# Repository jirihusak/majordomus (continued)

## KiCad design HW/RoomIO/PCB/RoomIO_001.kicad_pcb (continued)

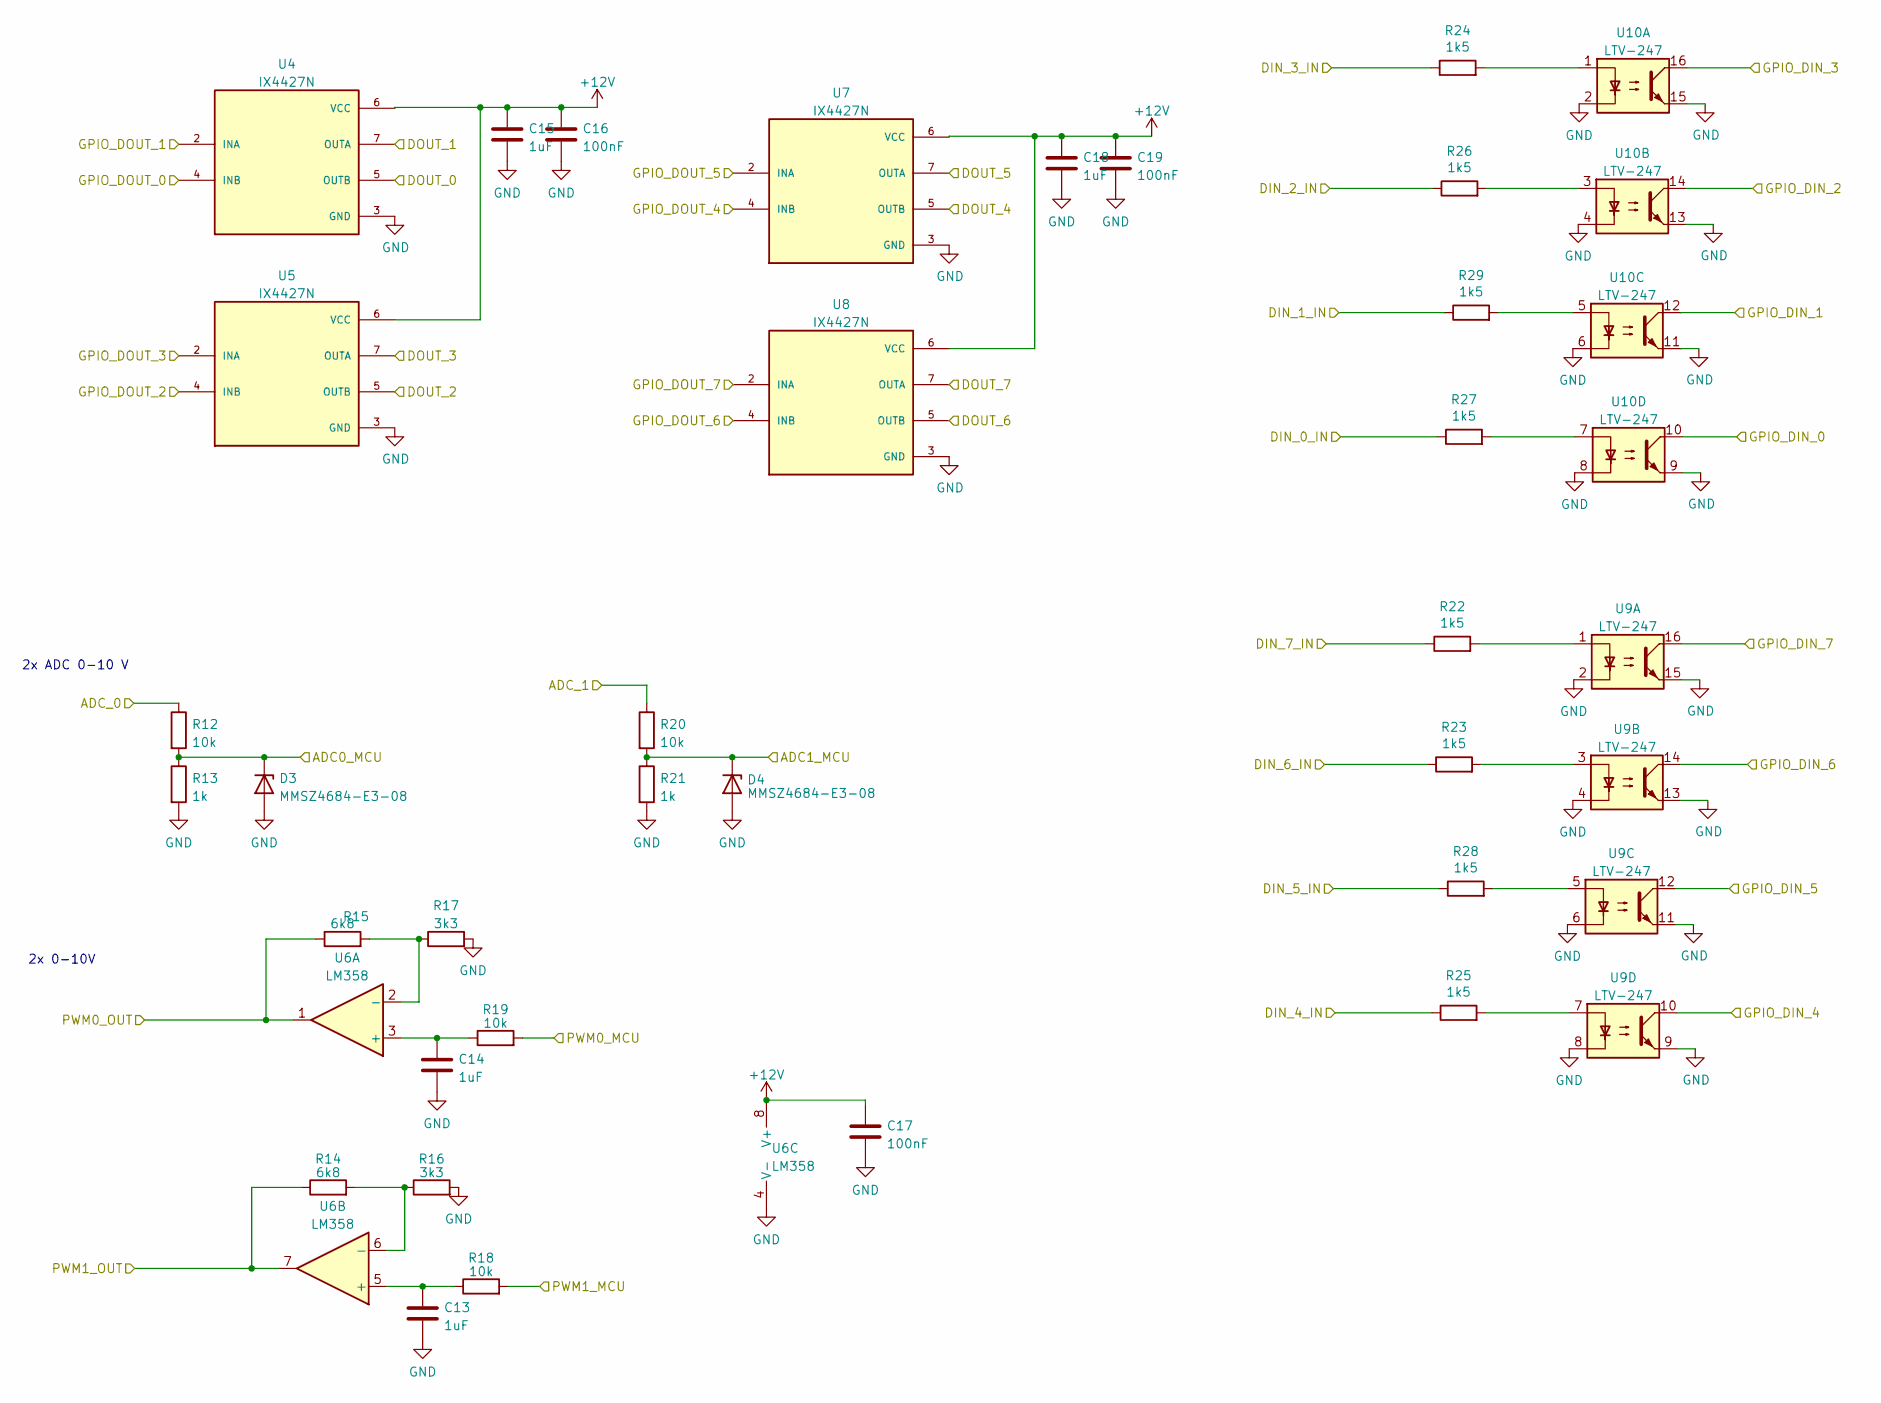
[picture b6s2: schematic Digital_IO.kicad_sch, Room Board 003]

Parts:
C13, C14, C15, C18: 1uF; C_0805_2012Metric
C16, C17, C19: 100nF; C_0805_2012Metric
D3, D4: MMSZ4684-E3-08; D_SOD-123
R12, R18, R19, R20: 10k; R_0805_2012Metric
R13, R21: 1k; R_0805_2012Metric
R14, R15: 6k8; R_0805_2012Metric
R16, R17: 3k3; R_0805_2012Metric
R22, R23, R24, R25, R26, R27, R28, R29: 1k5; R_0805_2012Metric
U4, U5, U7, U8: IX4427N; SOIC-8_3.9x4.9mm_P1.27mm
U6: LM358; TSSOP-8_4.4x3mm_P0.65mm
U9, U10: LTV-247; SOP-16_4.4x10.4mm_P1.27mm

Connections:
+12V: C15.1, C16.1, C17.1, C18.1, C19.1, U4.6 (VCC), U5.6 (VCC), U6.8 (V+), U7.6 (VCC), U8.6 (VCC); also elsewhere on the board
/Connectors/ADC_0: R12.1; also elsewhere on the board
/Connectors/ADC_1: R20.1; also elsewhere on the board
/Connectors/DAC_0: R15.1, U6.1; also elsewhere on the board
/Connectors/DAC_1: R14.1, U6.7; also elsewhere on the board
/Connectors/DIN_0: R27.1; also elsewhere on the board
/Connectors/DIN_1: R29.1; also elsewhere on the board
/Connectors/DIN_2: R26.1; also elsewhere on the board
/Connectors/DIN_3: R24.1; also elsewhere on the board
/Connectors/DIN_4: R25.1; also elsewhere on the board
/Connectors/DIN_5: R28.1; also elsewhere on the board
/Connectors/DIN_6: R23.1; also elsewhere on the board
/Connectors/DIN_7: R22.1; also elsewhere on the board
/Connectors/DOUT_0: U4.5 (OUTB); also elsewhere on the board
/Connectors/DOUT_1: U4.7 (OUTA); also elsewhere on the board
/Connectors/DOUT_2: U5.5 (OUTB); also elsewhere on the board
/Connectors/DOUT_3: U5.7 (OUTA); also elsewhere on the board
/Connectors/DOUT_4: U7.5 (OUTB); also elsewhere on the board
/Connectors/DOUT_5: U7.7 (OUTA); also elsewhere on the board
/Connectors/DOUT_6: U8.5 (OUTB); also elsewhere on the board
/Connectors/DOUT_7: U8.7 (OUTA); also elsewhere on the board
/Digital IO/ADC0_MCU: D3.1 (K), R12.2, R13.1; also elsewhere on the board
/Digital IO/ADC1_MCU: D4.1 (K), R20.2, R21.1; also elsewhere on the board
/Digital IO/GPIO_DIN_0: U10.10; also elsewhere on the board
/Digital IO/GPIO_DIN_1: U10.12; also elsewhere on the board
/Digital IO/GPIO_DIN_2: U10.14; also elsewhere on the board
/Digital IO/GPIO_DIN_3: U10.16; also elsewhere on the board
/Digital IO/GPIO_DIN_4: U9.10; also elsewhere on the board
/Digital IO/GPIO_DIN_5: U9.12; also elsewhere on the board
/Digital IO/GPIO_DIN_6: U9.14; also elsewhere on the board
/Digital IO/GPIO_DIN_7: U9.16; also elsewhere on the board
/Digital IO/GPIO_DOUT_0: U4.4 (INB); also elsewhere on the board
/Digital IO/GPIO_DOUT_1: U4.2 (INA); also elsewhere on the board
/Digital IO/GPIO_DOUT_2: U5.4 (INB); also elsewhere on the board
/Digital IO/GPIO_DOUT_3: U5.2 (INA); also elsewhere on the board
/Digital IO/GPIO_DOUT_4: U7.4 (INB); also elsewhere on the board
/Digital IO/GPIO_DOUT_5: U7.2 (INA); also elsewhere on the board
/Digital IO/GPIO_DOUT_6: U8.4 (INB); also elsewhere on the board
/Digital IO/GPIO_DOUT_7: U8.2 (INA); also elsewhere on the board
/Digital IO/PWM0_MCU: R19.2; also elsewhere on the board
/Digital IO/PWM1_MCU: R18.2; also elsewhere on the board
GND: C13.2, C14.2, C15.2, C16.2, C17.2, C18.2, C19.2, D3.2 (A), D4.2 (A), R13.2, R16.2, R17.2, R21.2, U4.3 (GND), U5.3 (GND), U6.4 (V-), U7.3 (GND), U8.3 (GND), U9.2, U9.4, U9.6, U9.8, U9.9, U9.11, U9.13, U9.15, U10.2, U10.4, U10.6, U10.8, U10.9, U10.11, U10.13, U10.15; also elsewhere on the board
unnamed: R22.2, U9.1
unnamed: R23.2, U9.3
unnamed: R24.2, U10.1
unnamed: R25.2, U9.7
unnamed: R26.2, U10.3
unnamed: R27.2, U10.7
unnamed: R28.2, U9.5
unnamed: R29.2, U10.5
unnamed: C14.1, R19.1, U6.3 (+)
unnamed: R15.2, R17.1, U6.2 (-)
unnamed: C13.1, R18.1, U6.5 (+)
unnamed: R14.2, R16.1, U6.6 (-)

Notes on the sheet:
2x 0-10V
2x ADC 0-10 V

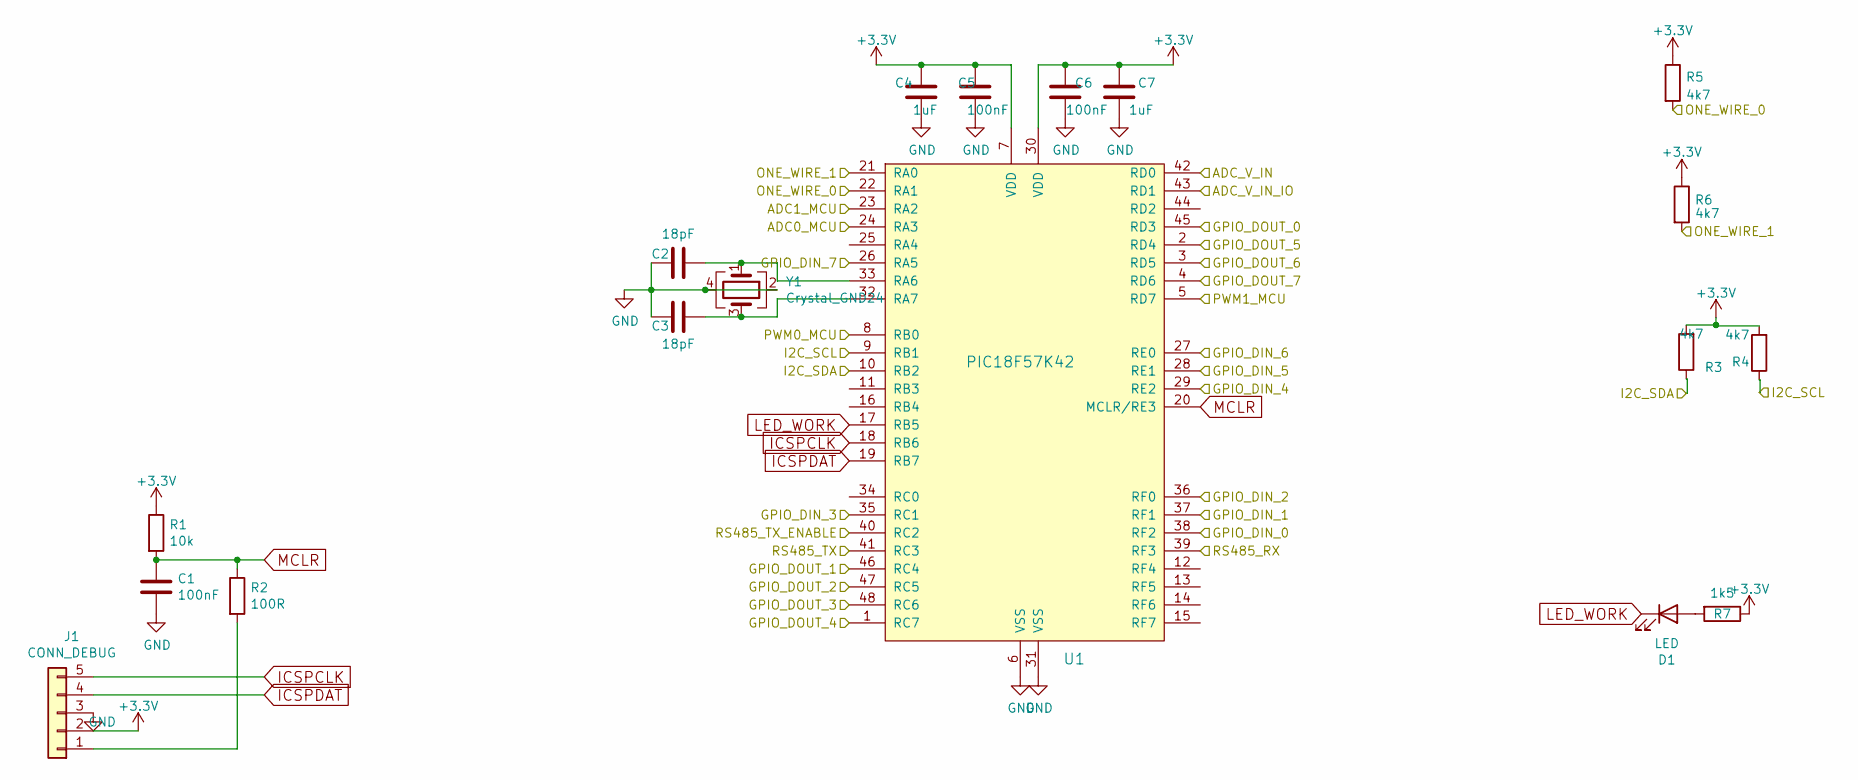
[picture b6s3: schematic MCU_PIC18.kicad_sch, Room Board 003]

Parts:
C1, C5, C6: 100nF; C_0805_2012Metric
C2, C3: 18pF; C_0805_2012Metric
C4, C7: 1uF; C_0805_2012Metric
D1: LED; LED_0805_2012Metric_Pad1.15x1.40mm_HandSolder
J1: CONN_DEBUG; PinHeader_1x05_P2.54mm_Vertical
R1: 10k; R_0805_2012Metric
R2: 100R; R_0805_2012Metric
R3, R4, R5, R6: 4k7; R_0805_2012Metric
R7: 1k5; R_0805_2012Metric
U1: PIC18F57K42; TQFP-48_7x7mm_P0.5mm
Y1: Crystal_GND24; Crystal_SMD_SeikoEpson_FA238-4Pin_3.2x2.5mm

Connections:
+3.3V: C4.1, C5.1, C6.1, C7.1, J1.2, R1.1, R3.2, R4.2, R5.1, R6.1, R7.1, U1.7 (VDD), U1.30 (VDD); also elsewhere on the board
/Connectors/I2C_SCL: R4.1, U1.9 (RB1); also elsewhere on the board
/Connectors/I2C_SDA: R3.1, U1.10 (RB2); also elsewhere on the board
/Connectors/ONE_WIRE_0: R5.2, U1.22 (RA1); also elsewhere on the board
/Connectors/ONE_WIRE_1: R6.2, U1.21 (RA0); also elsewhere on the board
/Digital IO/ADC0_MCU: U1.24 (RA3); also elsewhere on the board
/Digital IO/ADC1_MCU: U1.23 (RA2); also elsewhere on the board
/Digital IO/GPIO_DIN_0: U1.38 (RF2); also elsewhere on the board
/Digital IO/GPIO_DIN_1: U1.37 (RF1); also elsewhere on the board
/Digital IO/GPIO_DIN_2: U1.36 (RF0); also elsewhere on the board
/Digital IO/GPIO_DIN_3: U1.35 (RC1); also elsewhere on the board
/Digital IO/GPIO_DIN_4: U1.29 (RE2); also elsewhere on the board
/Digital IO/GPIO_DIN_5: U1.28 (RE1); also elsewhere on the board
/Digital IO/GPIO_DIN_6: U1.27 (RE0); also elsewhere on the board
/Digital IO/GPIO_DIN_7: U1.26 (RA5); also elsewhere on the board
/Digital IO/GPIO_DOUT_0: U1.45 (RD3); also elsewhere on the board
/Digital IO/GPIO_DOUT_1: U1.46 (RC4); also elsewhere on the board
/Digital IO/GPIO_DOUT_2: U1.47 (RC5); also elsewhere on the board
/Digital IO/GPIO_DOUT_3: U1.48 (RC6); also elsewhere on the board
/Digital IO/GPIO_DOUT_4: U1.1 (RC7); also elsewhere on the board
/Digital IO/GPIO_DOUT_5: U1.2 (RD4); also elsewhere on the board
/Digital IO/GPIO_DOUT_6: U1.3 (RD5); also elsewhere on the board
/Digital IO/GPIO_DOUT_7: U1.4 (RD6); also elsewhere on the board
/Digital IO/PWM0_MCU: U1.8 (RB0); also elsewhere on the board
/Digital IO/PWM1_MCU: U1.5 (RD7); also elsewhere on the board
/MCU_PIC18/ADC_V_IN: U1.42 (RD0); also elsewhere on the board
/MCU_PIC18/ADC_V_IN_IO: U1.43 (RD1); also elsewhere on the board
/MCU_PIC18/RS485_RX: U1.39 (RF3); also elsewhere on the board
/MCU_PIC18/RS485_TX: U1.41 (RC3); also elsewhere on the board
/MCU_PIC18/RS485_TX_ENABLE: U1.40 (RC2); also elsewhere on the board
GND: C1.2, C2.2, C3.2, C4.2, C5.2, C6.2, C7.2, J1.3, U1.6 (VSS), U1.31 (VSS), Y1.2, Y1.4; also elsewhere on the board
ICSPCLK: J1.5, U1.18 (RB6)
ICSPDAT: J1.4, U1.19 (RB7)
LED_WORK: D1.1 (K), U1.17 (RB5)
MCLR: C1.1, R1.2, R2.1, U1.20 (MCLR/RE3)
unnamed: D1.2 (A), R7.2
unnamed: J1.1, R2.2
unnamed: C2.1, U1.33 (RA6), Y1.1
unnamed: C3.1, U1.32 (RA7), Y1.3

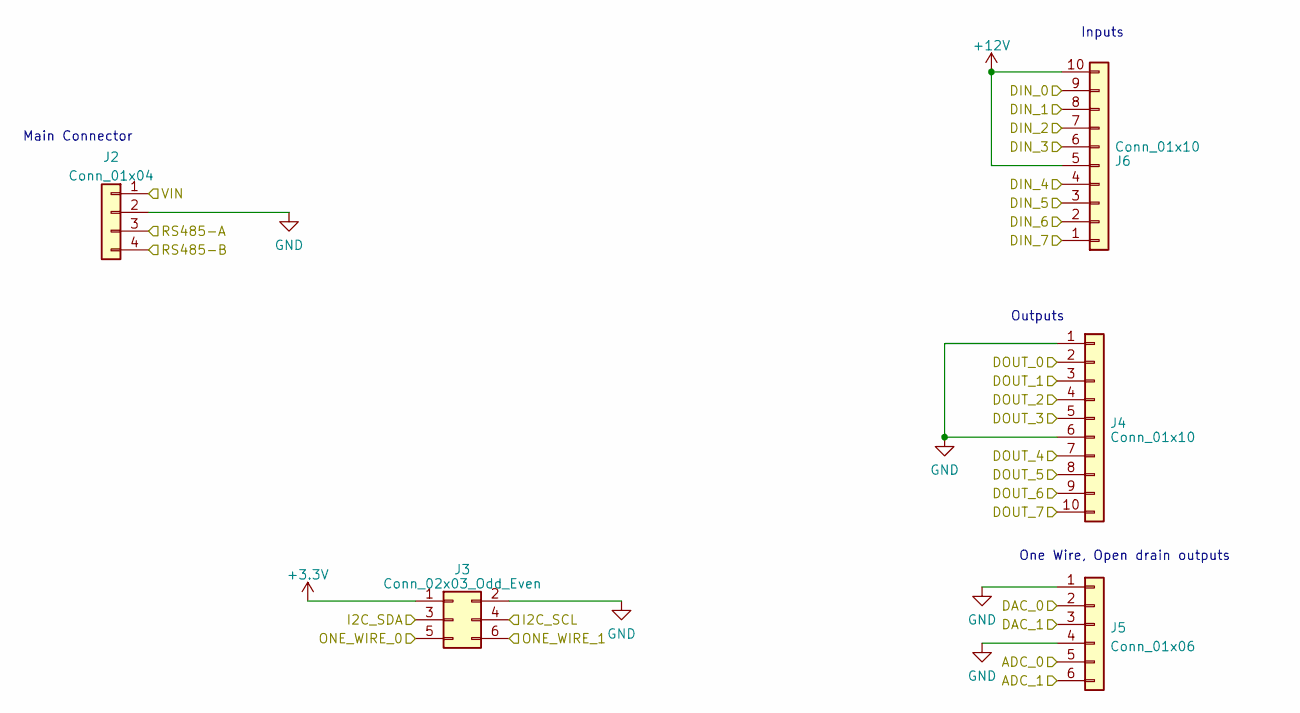
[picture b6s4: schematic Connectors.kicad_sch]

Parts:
J2: Conn_01x04; PhoenixContact_MSTBVA_2,5_4-G_1x04_P5.00mm_Vertical
J3: Conn_02x03_Odd_Even; PinSocket_2x03_P2.54mm_Vertical
J4, J6: Conn_01x10; PhoenixContact_MCV_1,5_10-G-3.5_1x10_P3.50mm_Vertical
J5: Conn_01x06; PhoenixContact_MCV_1,5_6-G-3.5_1x06_P3.50mm_Vertical

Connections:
+3.3V: J3.1; also elsewhere on the board
+12V: J6.5, J6.10; also elsewhere on the board
/Connectors/ADC_0: J5.5; also elsewhere on the board
/Connectors/ADC_1: J5.6; also elsewhere on the board
/Connectors/DAC_0: J5.2; also elsewhere on the board
/Connectors/DAC_1: J5.3; also elsewhere on the board
/Connectors/DIN_0: J6.9; also elsewhere on the board
/Connectors/DIN_1: J6.8; also elsewhere on the board
/Connectors/DIN_2: J6.7; also elsewhere on the board
/Connectors/DIN_3: J6.6; also elsewhere on the board
/Connectors/DIN_4: J6.4; also elsewhere on the board
/Connectors/DIN_5: J6.3; also elsewhere on the board
/Connectors/DIN_6: J6.2; also elsewhere on the board
/Connectors/DIN_7: J6.1; also elsewhere on the board
/Connectors/DOUT_0: J4.2; also elsewhere on the board
/Connectors/DOUT_1: J4.3; also elsewhere on the board
/Connectors/DOUT_2: J4.4; also elsewhere on the board
/Connectors/DOUT_3: J4.5; also elsewhere on the board
/Connectors/DOUT_4: J4.7; also elsewhere on the board
/Connectors/DOUT_5: J4.8; also elsewhere on the board
/Connectors/DOUT_6: J4.9; also elsewhere on the board
/Connectors/DOUT_7: J4.10; also elsewhere on the board
/Connectors/I2C_SCL: J3.4; also elsewhere on the board
/Connectors/I2C_SDA: J3.3; also elsewhere on the board
/Connectors/ONE_WIRE_0: J3.5; also elsewhere on the board
/Connectors/ONE_WIRE_1: J3.6; also elsewhere on the board
/Connectors/RS485-A: J2.3; also elsewhere on the board
/Connectors/RS485-B: J2.4; also elsewhere on the board
/Connectors/VIN: J2.1; also elsewhere on the board
GND: J2.2, J3.2, J4.1, J4.6, J5.1, J5.4; also elsewhere on the board

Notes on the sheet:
Inputs
Main Connector
One Wire, Open drain outputs
Outputs

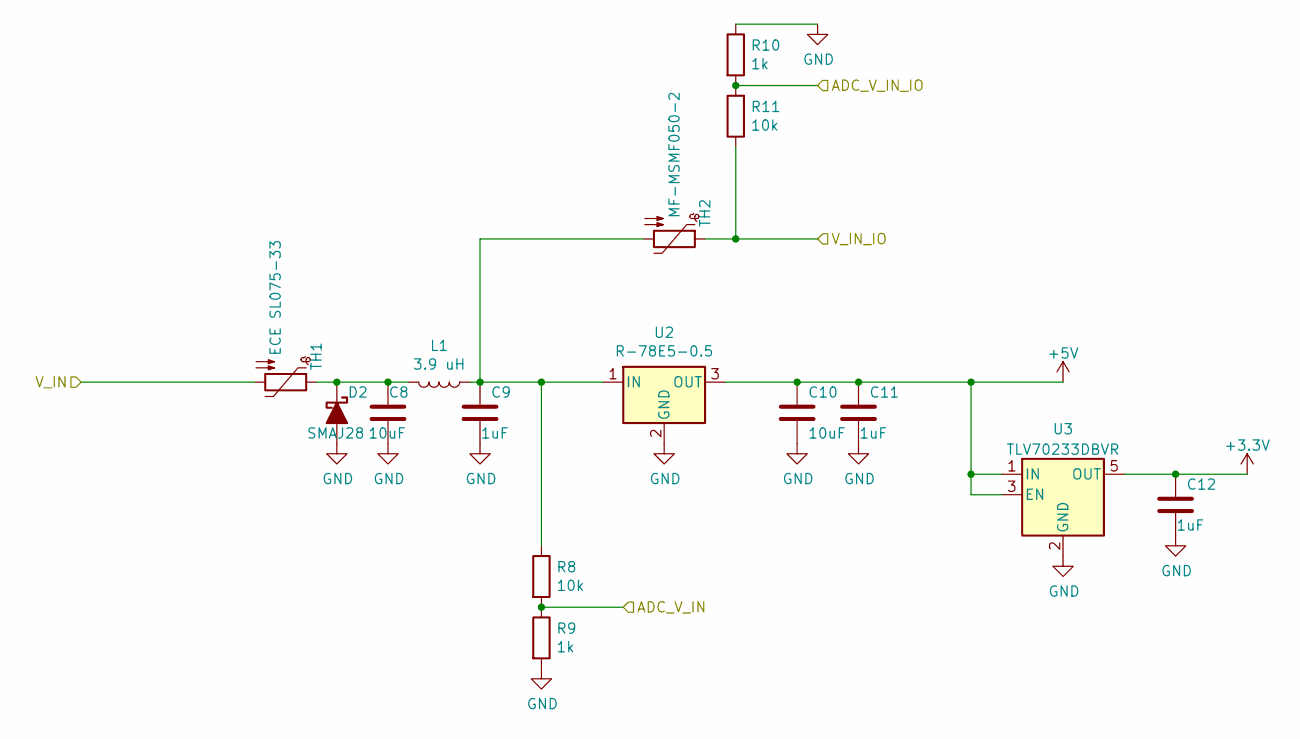
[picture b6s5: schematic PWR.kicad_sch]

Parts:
C8, C10: 10uF; C_1210_3225Metric
C9, C11, C12: 1uF; C_0805_2012Metric
D2: SMAJ28; D_SMA
L1: 3.9 uH; L_0805_2012Metric_Pad1.15x1.40mm_HandSolder
R8, R11: 10k; R_0805_2012Metric
R9, R10: 1k; R_0805_2012Metric
TH1: ECE SL075-33; Fuse_1812_4532Metric_Pad1.30x3.40mm_HandSolder
TH2: MF-MSMF050-2; Fuse_1812_4532Metric_Pad1.30x3.40mm_HandSolder
U2: R-78E5-0.5; Converter_DCDC_RECOM_R-78E-0.5_THT
U3: TLV70233DBVR; SOT-23-5

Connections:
+3.3V: C12.1, U3.5 (OUT); also elsewhere on the board
+5V: C10.1, C11.1, U2.3 (OUT), U3.1 (IN), U3.3 (EN); also elsewhere on the board
+12V: R11.1, TH2.1; also elsewhere on the board
/Connectors/VIN: TH1.2; also elsewhere on the board
/MCU_PIC18/ADC_V_IN: R8.2, R9.1; also elsewhere on the board
/MCU_PIC18/ADC_V_IN_IO: R10.2, R11.2; also elsewhere on the board
GND: C8.2, C9.2, C10.2, C11.2, C12.2, D2.2 (A), R9.2, R10.1, U2.2 (GND), U3.2 (GND); also elsewhere on the board
unnamed: C8.1, D2.1 (K), L1.2, TH1.1
unnamed: C9.1, L1.1, R8.1, TH2.2, U2.1 (IN)

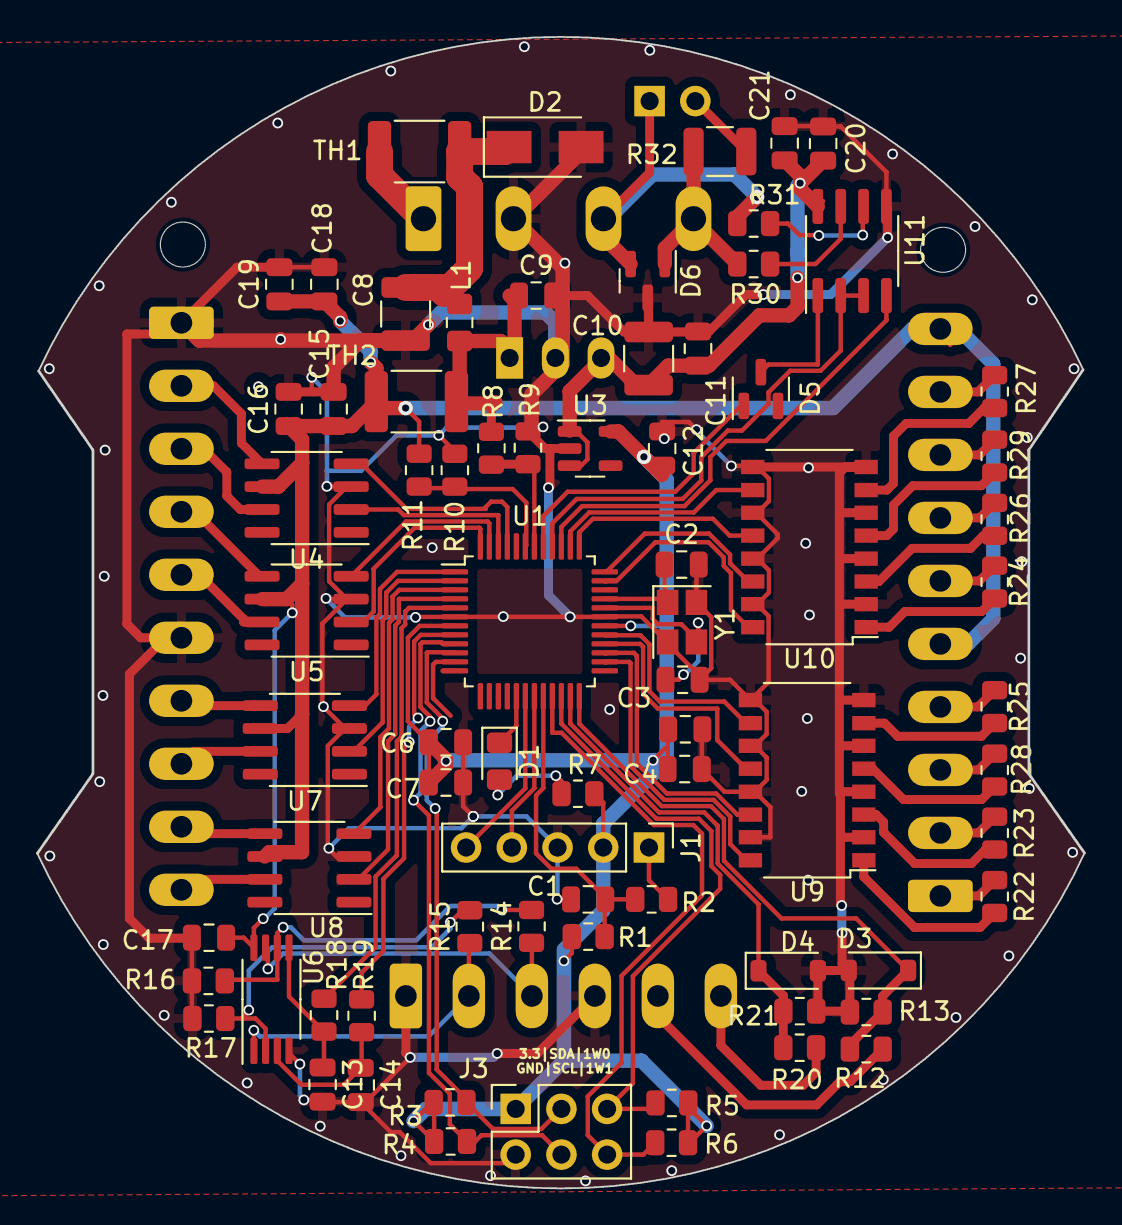
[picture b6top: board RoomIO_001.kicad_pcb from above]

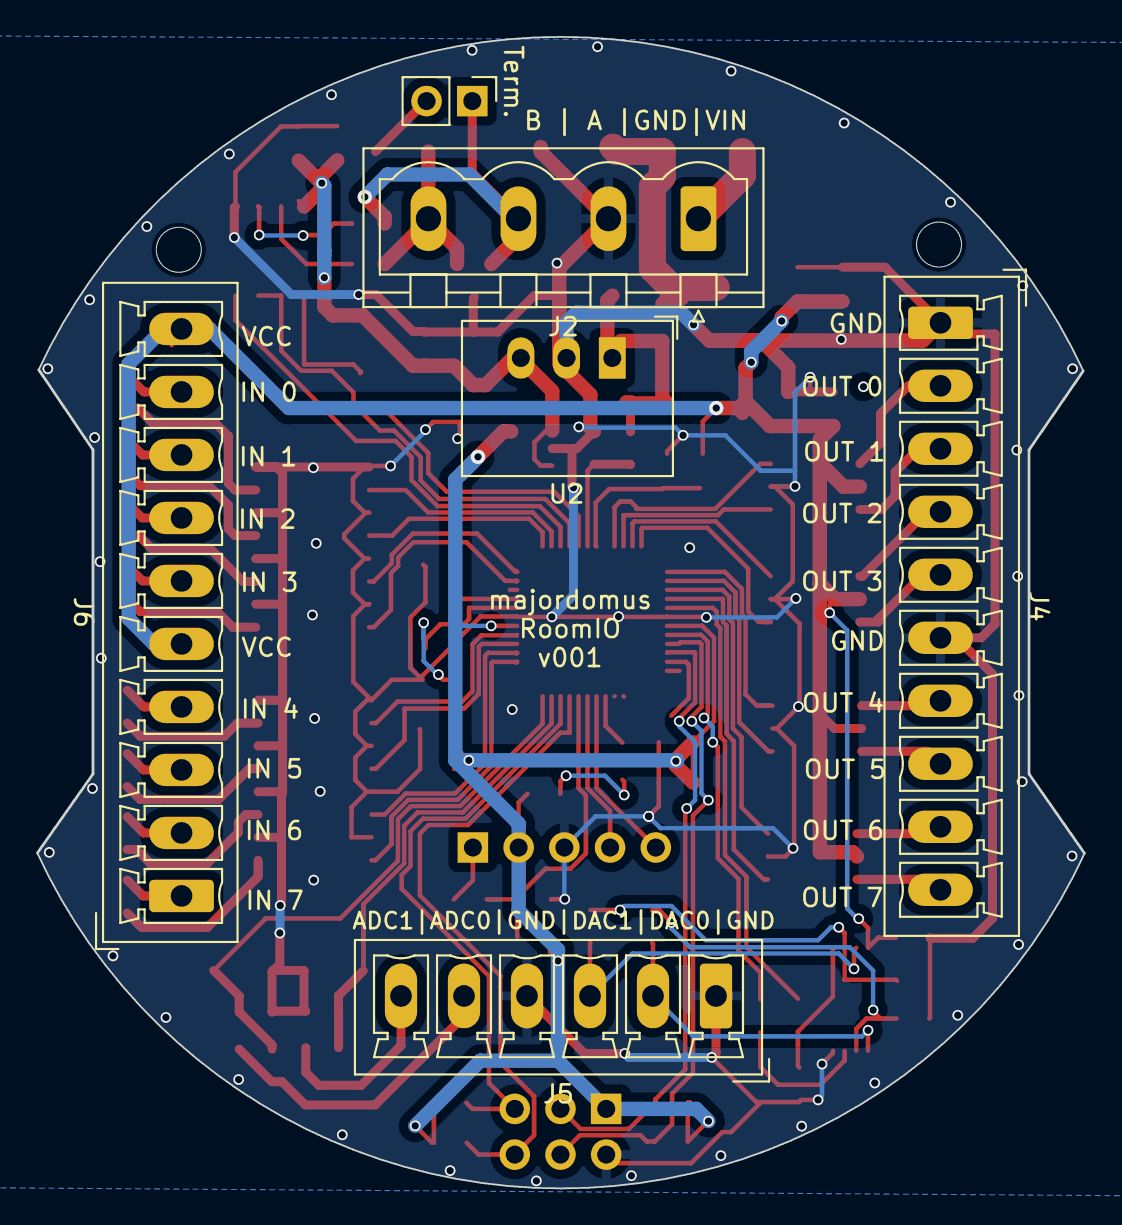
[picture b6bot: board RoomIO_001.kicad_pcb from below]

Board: 2 copper layers, 58.2 x 63.9 mm, 83 parts (6 on the bottom side), 82 nets.

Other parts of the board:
 : MountingHole_2.5mm
 #2: MountingHole_2.5mm
Term.: Jumper; PinHeader_1x02_P2.54mm_Vertical

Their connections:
/Connectors/RS485-A: Term..1; also elsewhere on the board
unnamed 64: Term..2; also elsewhere on the board

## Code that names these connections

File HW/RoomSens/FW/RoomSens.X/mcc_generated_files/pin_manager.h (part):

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#define RA0_SetHigh()            do { LATAbits.LATA0 = 1; } while(0)
#define RA0_SetLow()             do { LATAbits.LATA0 = 0; } while(0)
#define RA0_Toggle()             do { LATAbits.LATA0 = ~LATAbits.LATA0; } while(0)
#define RA0_GetValue()              PORTAbits.RA0
#define RA0_SetDigitalInput()    do { TRISAbits.TRISA0 = 1; } while(0)
#define RA0_SetDigitalOutput()   do { TRISAbits.TRISA0 = 0; } while(0)
#define RA0_SetPullup()             do { WPUAbits.WPUA0 = 1; } while(0)
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// get/set ONE_WIRE_1 aliases
#define ONE_WIRE_1_TRIS                 TRISAbits.TRISA1
#define ONE_WIRE_1_LAT                  LATAbits.LATA1
#define ONE_WIRE_1_PORT                 PORTAbits.RA1
#define ONE_WIRE_1_WPU                  WPUAbits.WPUA1
#define ONE_WIRE_1_OD                   ODCONAbits.ODCA1
#define ONE_WIRE_1_ANS                  ANSELAbits.ANSELA1
#define ONE_WIRE_1_SetHigh()            do { LATAbits.LATA1 = 1; } while(0)
#define ONE_WIRE_1_SetLow()             do { LATAbits.LATA1 = 0; } while(0)
#define ONE_WIRE_1_Toggle()             do { LATAbits.LATA1 = ~LATAbits.LATA1; } while(0)
#define ONE_WIRE_1_GetValue()           PORTAbits.RA1
#define ONE_WIRE_1_SetDigitalInput()    do { TRISAbits.TRISA1 = 1; } while(0)
#define ONE_WIRE_1_SetDigitalOutput()   do { TRISAbits.TRISA1 = 0; } while(0)
#define ONE_WIRE_1_SetPullup()          do { WPUAbits.WPUA1 = 1; } while(0)
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// get/set PIR_SIGNAL aliases
#define PIR_SIGNAL_TRIS                 TRISAbits.TRISA2
#define PIR_SIGNAL_LAT                  LATAbits.LATA2
#define PIR_SIGNAL_PORT                 PORTAbits.RA2
#define PIR_SIGNAL_WPU                  WPUAbits.WPUA2
#define PIR_SIGNAL_OD                   ODCONAbits.ODCA2
#define PIR_SIGNAL_ANS                  ANSELAbits.ANSELA2
#define PIR_SIGNAL_SetHigh()            do { LATAbits.LATA2 = 1; } while(0)
#define PIR_SIGNAL_SetLow()             do { LATAbits.LATA2 = 0; } while(0)
#define PIR_SIGNAL_Toggle()             do { LATAbits.LATA2 = ~LATAbits.LATA2; } while(0)
#define PIR_SIGNAL_GetValue()           PORTAbits.RA2
#define PIR_SIGNAL_SetDigitalInput()    do { TRISAbits.TRISA2 = 1; } while(0)
#define PIR_SIGNAL_SetDigitalOutput()   do { TRISAbits.TRISA2 = 0; } while(0)
#define PIR_SIGNAL_SetPullup()          do { WPUAbits.WPUA2 = 1; } while(0)
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#define RA3_SetHigh()            do { LATAbits.LATA3 = 1; } while(0)
#define RA3_SetLow()             do { LATAbits.LATA3 = 0; } while(0)
#define RA3_Toggle()             do { LATAbits.LATA3 = ~LATAbits.LATA3; } while(0)
#define RA3_GetValue()              PORTAbits.RA3
#define RA3_SetDigitalInput()    do { TRISAbits.TRISA3 = 1; } while(0)
#define RA3_SetDigitalOutput()   do { TRISAbits.TRISA3 = 0; } while(0)
#define RA3_SetPullup()             do { WPUAbits.WPUA3 = 1; } while(0)
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// get/set I2C_SCL aliases
#define I2C_SCL_TRIS                 TRISAbits.TRISA4
#define I2C_SCL_LAT                  LATAbits.LATA4
#define I2C_SCL_PORT                 PORTAbits.RA4
#define I2C_SCL_WPU                  WPUAbits.WPUA4
#define I2C_SCL_OD                   ODCONAbits.ODCA4
#define I2C_SCL_ANS                  ANSELAbits.ANSELA4
#define I2C_SCL_SetHigh()            do { LATAbits.LATA4 = 1; } while(0)
#define I2C_SCL_SetLow()             do { LATAbits.LATA4 = 0; } while(0)
#define I2C_SCL_Toggle()             do { LATAbits.LATA4 = ~LATAbits.LATA4; } while(0)
#define I2C_SCL_GetValue()           PORTAbits.RA4
#define I2C_SCL_SetDigitalInput()    do { TRISAbits.TRISA4 = 1; } while(0)
#define I2C_SCL_SetDigitalOutput()   do { TRISAbits.TRISA4 = 0; } while(0)
#define I2C_SCL_SetPullup()          do { WPUAbits.WPUA4 = 1; } while(0)
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// get/set I2C_SDA aliases
#define I2C_SDA_TRIS                 TRISAbits.TRISA5
#define I2C_SDA_LAT                  LATAbits.LATA5
#define I2C_SDA_PORT                 PORTAbits.RA5
#define I2C_SDA_WPU                  WPUAbits.WPUA5
#define I2C_SDA_OD                   ODCONAbits.ODCA5
#define I2C_SDA_ANS                  ANSELAbits.ANSELA5
#define I2C_SDA_SetHigh()            do { LATAbits.LATA5 = 1; } while(0)
#define I2C_SDA_SetLow()             do { LATAbits.LATA5 = 0; } while(0)
#define I2C_SDA_Toggle()             do { LATAbits.LATA5 = ~LATAbits.LATA5; } while(0)
#define I2C_SDA_GetValue()           PORTAbits.RA5
#define I2C_SDA_SetDigitalInput()    do { TRISAbits.TRISA5 = 1; } while(0)
#define I2C_SDA_SetDigitalOutput()   do { TRISAbits.TRISA5 = 0; } while(0)
#define I2C_SDA_SetPullup()          do { WPUAbits.WPUA5 = 1; } while(0)
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#define RB0_SetHigh()            do { LATBbits.LATB0 = 1; } while(0)
#define RB0_SetLow()             do { LATBbits.LATB0 = 0; } while(0)
#define RB0_Toggle()             do { LATBbits.LATB0 = ~LATBbits.LATB0; } while(0)
#define RB0_GetValue()              PORTBbits.RB0
#define RB0_SetDigitalInput()    do { TRISBbits.TRISB0 = 1; } while(0)
#define RB0_SetDigitalOutput()   do { TRISBbits.TRISB0 = 0; } while(0)
#define RB0_SetPullup()             do { WPUBbits.WPUB0 = 1; } while(0)
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// get/set LCD_A0 aliases
#define LCD_A0_TRIS                 TRISBbits.TRISB1
#define LCD_A0_LAT                  LATBbits.LATB1
#define LCD_A0_PORT                 PORTBbits.RB1
#define LCD_A0_WPU                  WPUBbits.WPUB1
#define LCD_A0_OD                   ODCONBbits.ODCB1
#define LCD_A0_ANS                  ANSELBbits.ANSELB1
#define LCD_A0_SetHigh()            do { LATBbits.LATB1 = 1; } while(0)
#define LCD_A0_SetLow()             do { LATBbits.LATB1 = 0; } while(0)
#define LCD_A0_Toggle()             do { LATBbits.LATB1 = ~LATBbits.LATB1; } while(0)
#define LCD_A0_GetValue()           PORTBbits.RB1
#define LCD_A0_SetDigitalInput()    do { TRISBbits.TRISB1 = 1; } while(0)
#define LCD_A0_SetDigitalOutput()   do { TRISBbits.TRISB1 = 0; } while(0)
#define LCD_A0_SetPullup()          do { WPUBbits.WPUB1 = 1; } while(0)
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#define RB2_SetHigh()            do { LATBbits.LATB2 = 1; } while(0)
#define RB2_SetLow()             do { LATBbits.LATB2 = 0; } while(0)
#define RB2_Toggle()             do { LATBbits.LATB2 = ~LATBbits.LATB2; } while(0)
#define RB2_GetValue()              PORTBbits.RB2
#define RB2_SetDigitalInput()    do { TRISBbits.TRISB2 = 1; } while(0)
#define RB2_SetDigitalOutput()   do { TRISBbits.TRISB2 = 0; } while(0)
#define RB2_SetPullup()             do { WPUBbits.WPUB2 = 1; } while(0)
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#define RB3_SetHigh()            do { LATBbits.LATB3 = 1; } while(0)
#define RB3_SetLow()             do { LATBbits.LATB3 = 0; } while(0)
#define RB3_Toggle()             do { LATBbits.LATB3 = ~LATBbits.LATB3; } while(0)
#define RB3_GetValue()              PORTBbits.RB3
#define RB3_SetDigitalInput()    do { TRISBbits.TRISB3 = 1; } while(0)
#define RB3_SetDigitalOutput()   do { TRISBbits.TRISB3 = 0; } while(0)
#define RB3_SetPullup()             do { WPUBbits.WPUB3 = 1; } while(0)
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// get/set LED_AMBIENT aliases
#define LED_AMBIENT_TRIS                 TRISBbits.TRISB4
#define LED_AMBIENT_LAT                  LATBbits.LATB4
#define LED_AMBIENT_PORT                 PORTBbits.RB4
#define LED_AMBIENT_WPU                  WPUBbits.WPUB4
#define LED_AMBIENT_OD                   ODCONBbits.ODCB4
#define LED_AMBIENT_ANS                  ANSELBbits.ANSELB4
#define LED_AMBIENT_SetHigh()            do { LATBbits.LATB4 = 1; } while(0)
#define LED_AMBIENT_SetLow()             do { LATBbits.LATB4 = 0; } while(0)
#define LED_AMBIENT_Toggle()             do { LATBbits.LATB4 = ~LATBbits.LATB4; } while(0)
#define LED_AMBIENT_GetValue()           PORTBbits.RB4
#define LED_AMBIENT_SetDigitalInput()    do { TRISBbits.TRISB4 = 1; } while(0)
#define LED_AMBIENT_SetDigitalOutput()   do { TRISBbits.TRISB4 = 0; } while(0)
#define LED_AMBIENT_SetPullup()          do { WPUBbits.WPUB4 = 1; } while(0)
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// get/set LED_WORK aliases
#define LED_WORK_TRIS                 TRISBbits.TRISB5
#define LED_WORK_LAT                  LATBbits.LATB5
#define LED_WORK_PORT                 PORTBbits.RB5
#define LED_WORK_WPU                  WPUBbits.WPUB5
#define LED_WORK_OD                   ODCONBbits.ODCB5
#define LED_WORK_ANS                  ANSELBbits.ANSELB5
#define LED_WORK_SetHigh()            do { LATBbits.LATB5 = 1; } while(0)
#define LED_WORK_SetLow()             do { LATBbits.LATB5 = 0; } while(0)
#define LED_WORK_Toggle()             do { LATBbits.LATB5 = ~LATBbits.LATB5; } while(0)
#define LED_WORK_GetValue()           PORTBbits.RB5
#define LED_WORK_SetDigitalInput()    do { TRISBbits.TRISB5 = 1; } while(0)
#define LED_WORK_SetDigitalOutput()   do { TRISBbits.TRISB5 = 0; } while(0)
#define LED_WORK_SetPullup()          do { WPUBbits.WPUB5 = 1; } while(0)
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// get/set UNUSED aliases
#define UNUSED_TRIS                 TRISCbits.TRISC0
#define UNUSED_LAT                  LATCbits.LATC0
#define UNUSED_PORT                 PORTCbits.RC0
#define UNUSED_WPU                  WPUCbits.WPUC0
#define UNUSED_OD                   ODCONCbits.ODCC0
#define UNUSED_ANS                  ANSELCbits.ANSELC0
#define UNUSED_SetHigh()            do { LATCbits.LATC0 = 1; } while(0)
#define UNUSED_SetLow()             do { LATCbits.LATC0 = 0; } while(0)
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
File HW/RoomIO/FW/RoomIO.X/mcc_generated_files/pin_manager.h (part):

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// get/set ONE_WIRE_1 aliases
#define ONE_WIRE_1_TRIS                 TRISAbits.TRISA0
#define ONE_WIRE_1_LAT                  LATAbits.LATA0
#define ONE_WIRE_1_PORT                 PORTAbits.RA0
#define ONE_WIRE_1_WPU                  WPUAbits.WPUA0
#define ONE_WIRE_1_OD                   ODCONAbits.ODCA0
#define ONE_WIRE_1_ANS                  ANSELAbits.ANSELA0
#define ONE_WIRE_1_SetHigh()            do { LATAbits.LATA0 = 1; } while(0)
#define ONE_WIRE_1_SetLow()             do { LATAbits.LATA0 = 0; } while(0)
#define ONE_WIRE_1_Toggle()             do { LATAbits.LATA0 = ~LATAbits.LATA0; } while(0)
#define ONE_WIRE_1_GetValue()           PORTAbits.RA0
#define ONE_WIRE_1_SetDigitalInput()    do { TRISAbits.TRISA0 = 1; } while(0)
#define ONE_WIRE_1_SetDigitalOutput()   do { TRISAbits.TRISA0 = 0; } while(0)
#define ONE_WIRE_1_SetPullup()          do { WPUAbits.WPUA0 = 1; } while(0)
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// get/set ONE_WIRE_0 aliases
#define ONE_WIRE_0_TRIS                 TRISAbits.TRISA1
#define ONE_WIRE_0_LAT                  LATAbits.LATA1
#define ONE_WIRE_0_PORT                 PORTAbits.RA1
#define ONE_WIRE_0_WPU                  WPUAbits.WPUA1
#define ONE_WIRE_0_OD                   ODCONAbits.ODCA1
#define ONE_WIRE_0_ANS                  ANSELAbits.ANSELA1
#define ONE_WIRE_0_SetHigh()            do { LATAbits.LATA1 = 1; } while(0)
#define ONE_WIRE_0_SetLow()             do { LATAbits.LATA1 = 0; } while(0)
#define ONE_WIRE_0_Toggle()             do { LATAbits.LATA1 = ~LATAbits.LATA1; } while(0)
#define ONE_WIRE_0_GetValue()           PORTAbits.RA1
#define ONE_WIRE_0_SetDigitalInput()    do { TRISAbits.TRISA1 = 1; } while(0)
#define ONE_WIRE_0_SetDigitalOutput()   do { TRISAbits.TRISA1 = 0; } while(0)
#define ONE_WIRE_0_SetPullup()          do { WPUAbits.WPUA1 = 1; } while(0)
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// get/set ADC_1 aliases
#define ADC_1_TRIS                 TRISAbits.TRISA2
#define ADC_1_LAT                  LATAbits.LATA2
#define ADC_1_PORT                 PORTAbits.RA2
#define ADC_1_WPU                  WPUAbits.WPUA2
#define ADC_1_OD                   ODCONAbits.ODCA2
#define ADC_1_ANS                  ANSELAbits.ANSELA2
#define ADC_1_SetHigh()            do { LATAbits.LATA2 = 1; } while(0)
#define ADC_1_SetLow()             do { LATAbits.LATA2 = 0; } while(0)
#define ADC_1_Toggle()             do { LATAbits.LATA2 = ~LATAbits.LATA2; } while(0)
#define ADC_1_GetValue()           PORTAbits.RA2
#define ADC_1_SetDigitalInput()    do { TRISAbits.TRISA2 = 1; } while(0)
#define ADC_1_SetDigitalOutput()   do { TRISAbits.TRISA2 = 0; } while(0)
#define ADC_1_SetPullup()          do { WPUAbits.WPUA2 = 1; } while(0)
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// get/set ADC_0 aliases
#define ADC_0_TRIS                 TRISAbits.TRISA3
#define ADC_0_LAT                  LATAbits.LATA3
#define ADC_0_PORT                 PORTAbits.RA3
#define ADC_0_WPU                  WPUAbits.WPUA3
#define ADC_0_OD                   ODCONAbits.ODCA3
#define ADC_0_ANS                  ANSELAbits.ANSELA3
#define ADC_0_SetHigh()            do { LATAbits.LATA3 = 1; } while(0)
#define ADC_0_SetLow()             do { LATAbits.LATA3 = 0; } while(0)
#define ADC_0_Toggle()             do { LATAbits.LATA3 = ~LATAbits.LATA3; } while(0)
#define ADC_0_GetValue()           PORTAbits.RA3
#define ADC_0_SetDigitalInput()    do { TRISAbits.TRISA3 = 1; } while(0)
#define ADC_0_SetDigitalOutput()   do { TRISAbits.TRISA3 = 0; } while(0)
#define ADC_0_SetPullup()          do { WPUAbits.WPUA3 = 1; } while(0)
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#define RA4_SetHigh()            do { LATAbits.LATA4 = 1; } while(0)
#define RA4_SetLow()             do { LATAbits.LATA4 = 0; } while(0)
#define RA4_Toggle()             do { LATAbits.LATA4 = ~LATAbits.LATA4; } while(0)
#define RA4_GetValue()              PORTAbits.RA4
#define RA4_SetDigitalInput()    do { TRISAbits.TRISA4 = 1; } while(0)
#define RA4_SetDigitalOutput()   do { TRISAbits.TRISA4 = 0; } while(0)
#define RA4_SetPullup()             do { WPUAbits.WPUA4 = 1; } while(0)
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// get/set DIN_7 aliases
#define DIN_7_TRIS                 TRISAbits.TRISA5
#define DIN_7_LAT                  LATAbits.LATA5
#define DIN_7_PORT                 PORTAbits.RA5
#define DIN_7_WPU                  WPUAbits.WPUA5
#define DIN_7_OD                   ODCONAbits.ODCA5
#define DIN_7_ANS                  ANSELAbits.ANSELA5
#define DIN_7_SetHigh()            do { LATAbits.LATA5 = 1; } while(0)
#define DIN_7_SetLow()             do { LATAbits.LATA5 = 0; } while(0)
#define DIN_7_Toggle()             do { LATAbits.LATA5 = ~LATAbits.LATA5; } while(0)
#define DIN_7_GetValue()           PORTAbits.RA5
#define DIN_7_SetDigitalInput()    do { TRISAbits.TRISA5 = 1; } while(0)
#define DIN_7_SetDigitalOutput()   do { TRISAbits.TRISA5 = 0; } while(0)
#define DIN_7_SetPullup()          do { WPUAbits.WPUA5 = 1; } while(0)
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#define RB0_SetHigh()            do { LATBbits.LATB0 = 1; } while(0)
#define RB0_SetLow()             do { LATBbits.LATB0 = 0; } while(0)
#define RB0_Toggle()             do { LATBbits.LATB0 = ~LATBbits.LATB0; } while(0)
#define RB0_GetValue()              PORTBbits.RB0
#define RB0_SetDigitalInput()    do { TRISBbits.TRISB0 = 1; } while(0)
#define RB0_SetDigitalOutput()   do { TRISBbits.TRISB0 = 0; } while(0)
#define RB0_SetPullup()             do { WPUBbits.WPUB0 = 1; } while(0)
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// get/set I2C_SCL aliases
#define I2C_SCL_TRIS                 TRISBbits.TRISB1
#define I2C_SCL_LAT                  LATBbits.LATB1
#define I2C_SCL_PORT                 PORTBbits.RB1
#define I2C_SCL_WPU                  WPUBbits.WPUB1
#define I2C_SCL_OD                   ODCONBbits.ODCB1
#define I2C_SCL_ANS                  ANSELBbits.ANSELB1
#define I2C_SCL_SetHigh()            do { LATBbits.LATB1 = 1; } while(0)
#define I2C_SCL_SetLow()             do { LATBbits.LATB1 = 0; } while(0)
#define I2C_SCL_Toggle()             do { LATBbits.LATB1 = ~LATBbits.LATB1; } while(0)
#define I2C_SCL_GetValue()           PORTBbits.RB1
#define I2C_SCL_SetDigitalInput()    do { TRISBbits.TRISB1 = 1; } while(0)
#define I2C_SCL_SetDigitalOutput()   do { TRISBbits.TRISB1 = 0; } while(0)
#define I2C_SCL_SetPullup()          do { WPUBbits.WPUB1 = 1; } while(0)
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// get/set I2C_SDA aliases
#define I2C_SDA_TRIS                 TRISBbits.TRISB2
#define I2C_SDA_LAT                  LATBbits.LATB2
#define I2C_SDA_PORT                 PORTBbits.RB2
#define I2C_SDA_WPU                  WPUBbits.WPUB2
#define I2C_SDA_OD                   ODCONBbits.ODCB2
#define I2C_SDA_ANS                  ANSELBbits.ANSELB2
#define I2C_SDA_SetHigh()            do { LATBbits.LATB2 = 1; } while(0)
#define I2C_SDA_SetLow()             do { LATBbits.LATB2 = 0; } while(0)
#define I2C_SDA_Toggle()             do { LATBbits.LATB2 = ~LATBbits.LATB2; } while(0)
#define I2C_SDA_GetValue()           PORTBbits.RB2
#define I2C_SDA_SetDigitalInput()    do { TRISBbits.TRISB2 = 1; } while(0)
#define I2C_SDA_SetDigitalOutput()   do { TRISBbits.TRISB2 = 0; } while(0)
#define I2C_SDA_SetPullup()          do { WPUBbits.WPUB2 = 1; } while(0)
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// get/set LED_WORK aliases
#define LED_WORK_TRIS                 TRISBbits.TRISB5
#define LED_WORK_LAT                  LATBbits.LATB5
#define LED_WORK_PORT                 PORTBbits.RB5
#define LED_WORK_WPU                  WPUBbits.WPUB5
#define LED_WORK_OD                   ODCONBbits.ODCB5
#define LED_WORK_ANS                  ANSELBbits.ANSELB5
#define LED_WORK_SetHigh()            do { LATBbits.LATB5 = 1; } while(0)
#define LED_WORK_SetLow()             do { LATBbits.LATB5 = 0; } while(0)
#define LED_WORK_Toggle()             do { LATBbits.LATB5 = ~LATBbits.LATB5; } while(0)
#define LED_WORK_GetValue()           PORTBbits.RB5
#define LED_WORK_SetDigitalInput()    do { TRISBbits.TRISB5 = 1; } while(0)
#define LED_WORK_SetDigitalOutput()   do { TRISBbits.TRISB5 = 0; } while(0)
#define LED_WORK_SetPullup()          do { WPUBbits.WPUB5 = 1; } while(0)
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#define RC0_SetHigh()            do { LATCbits.LATC0 = 1; } while(0)
#define RC0_SetLow()             do { LATCbits.LATC0 = 0; } while(0)
#define RC0_Toggle()             do { LATCbits.LATC0 = ~LATCbits.LATC0; } while(0)
#define RC0_GetValue()              PORTCbits.RC0
#define RC0_SetDigitalInput()    do { TRISCbits.TRISC0 = 1; } while(0)
#define RC0_SetDigitalOutput()   do { TRISCbits.TRISC0 = 0; } while(0)
#define RC0_SetPullup()             do { WPUCbits.WPUC0 = 1; } while(0)
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// get/set DIN_3 aliases
#define DIN_3_TRIS                 TRISCbits.TRISC1
#define DIN_3_LAT                  LATCbits.LATC1
#define DIN_3_PORT                 PORTCbits.RC1
#define DIN_3_WPU                  WPUCbits.WPUC1
#define DIN_3_OD                   ODCONCbits.ODCC1
#define DIN_3_ANS                  ANSELCbits.ANSELC1
#define DIN_3_SetHigh()            do { LATCbits.LATC1 = 1; } while(0)
#define DIN_3_SetLow()             do { LATCbits.LATC1 = 0; } while(0)
#define DIN_3_Toggle()             do { LATCbits.LATC1 = ~LATCbits.LATC1; } while(0)
#define DIN_3_GetValue()           PORTCbits.RC1
#define DIN_3_SetDigitalInput()    do { TRISCbits.TRISC1 = 1; } while(0)
#define DIN_3_SetDigitalOutput()   do { TRISCbits.TRISC1 = 0; } while(0)
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
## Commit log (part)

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2023-12-19 RoomIO - PCB design and FW for PIC MCU
2023-12-19 RS4852USB - PCB design
2024-09-08 Add RoomSens Device, Add SW Majordomus Control - RS485 to MQTT Bridge
2024-11-29 SW Majordomus Control v 0.3.1
2024-11-29 FW - Room Sens v0.3, fix touch long press, display initialization, serial interface update
2024-12-10 Create Protocol Majordomus Rs-485 ASCII.md
    HW device RS485 protocol ASCII
2025-01-23 SW node-red
    add package node-red with scheduler
2025-01-24 update node-red help
2025-01-24 node-red help update image path
2025-01-27 fix table preview and licence
2025-03-19 Tiny sensor PCB and FW
2025-04-22 node-red light node
2025-04-28 fix scheduler evaluate outputs with priorities
2025-04-28 node-red scheduler fix evaluation and table preview
2025-04-30 node-red light node - add help, fix number of ouputs after reload page
2025-05-26 Create Protocol Majordomus Modbus.md
    Modbus protocol initial table
2025-08-27 Majordomus Control - split topic to specific pins
2025-11-27 RoomIO FW - support pulse counter
2025-12-06 MajordomusControl - add web interface, FW updates, Home Assistent config initial support
2025-12-24 change CRLF to LF endlines in run.sh script
2026-03-27 Add initial README documentation for Majordomus system
2026-03-28 Majordomus Control v 0.5, Home Assistant integration, protocol doc
2026-04-16 docs initial commit
2026-04-16 fix docs workflows
2026-04-16 doc - fix url sites
2026-04-16 docs - redirect
2026-04-16 initioal doc introduction
2026-04-16 Deployed 44f9286 with MkDocs version: 1.6.1
2026-05-22 Revise README for Majordomus project
    Updated the README to provide a comprehensive overview of Majordomus, including features, use cases, architecture, and hardware/software details.
2026-05-22 Enhance README with hardware details and images
    Added detailed descriptions and images for RoomSensor, BoxIO, and RoomIO.
2026-05-29 doc - overview, HW, Majordomus Control, node-red
2026-05-29 Update documentation link in README
    Updated documentation link in README.
2026-06-19 Add support for BoxIO HW, configuration - new autodetect all devices on bus, add double, tripple click, long click, HA integration
2026-06-28 majrodomus control - update relative path on web interface
2026-06-28 web redirect
2026-06-29 mqtt reconnect
2026-06-29 web interface entrya point
2026-06-29 edit redirect Web UI
